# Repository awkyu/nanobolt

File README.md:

# nanobolt
This project is a proposal for the design of an ablation probe for osteoid osteoma using a new ablation technique proposed by Pavitra Krishnaswamy, Andras Kuthi, P. Thomas Vernier, and Martin A. Gundersen [[1]](https://doi.org/10.1109/TDEI.2007.4286518).

Surgical resection and thermal ablation techniques have been shown to have suboptimal efficacy for the treatment of osteoid osteomas due to the high risk of complications and large ablation zones. Ablation technologies that utilize electric fields instead of thermal energy to produce nanosized pores in tumor cell membranes have been shown to be an attractive method for treating a wide variety of cancers due to the short ablation times and non-invasive nature of the procedure. We propose a nanosecond pulse electric field ablation system utilizing a pulse generator as a compact solution to ablate osteoid osteomas without harming the healthy bone, leading to reduced instances of post-operative complications. 

[1] P. Krishnaswamy, A. Kuthi, P. T. Vernier and M. A. Gundersen, "Compact Subnanosecond Pulse Generator Using Avalanche Transistors for Cell Electroperturbation Studies," IEEE Transactions on Dielectrics and Electrical Insulation, vol. 14, no. 4, pp. 873-877, Aug. 2007, doi: 10.1109/TDEI.2007.4286518.

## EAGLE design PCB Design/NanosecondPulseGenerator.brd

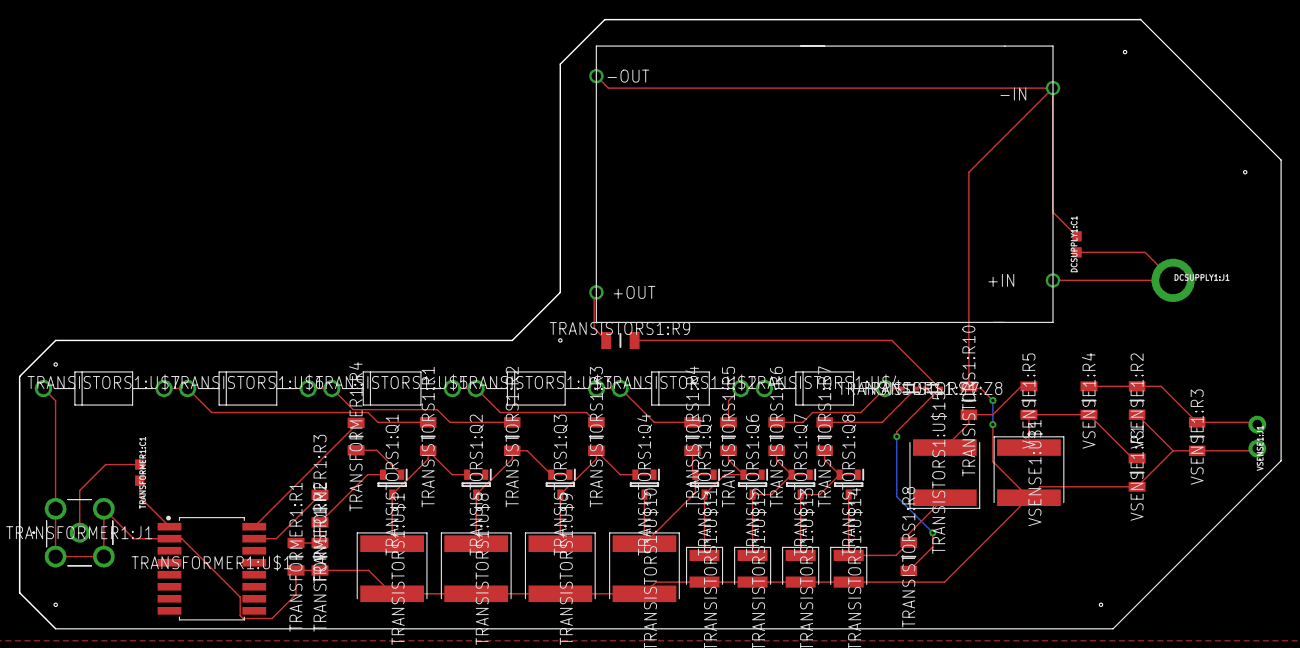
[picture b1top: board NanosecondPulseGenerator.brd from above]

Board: 2 copper layers, 133.3 x 64.4 mm, 52 parts (0 on the bottom side), 28 nets.

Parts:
DCSUPPLY1:C1: 0.1uF; 0603
DCSUPPLY1:J1: SNAP-FEMALE
DCSUPPLY1:U$1: DC-DCCONVERTER; DC-CONVERTER
TRANSFORMER1:C1: 10nF; 0603
TRANSFORMER1:J1: CONSMA008-G; CONSMA008G
TRANSFORMER1:R1, TRANSFORMER1:R2, TRANSFORMER1:R3, TRANSFORMER1:R4: CRCW12068R20FKEAHP; RESC3116X65N
TRANSFORMER1:U$1: TX1:1_QUAD; SOIC127P1067X508-16N
TRANSISTORS1:Q1, TRANSISTORS1:Q2, TRANSISTORS1:Q3, TRANSISTORS1:Q4, TRANSISTORS1:Q5, TRANSISTORS1:Q6, TRANSISTORS1:Q7, TRANSISTORS1:Q8: FMMT417TD; SOT96P240X110-3N
TRANSISTORS1:R1, TRANSISTORS1:R2, TRANSISTORS1:R3, TRANSISTORS1:R4, TRANSISTORS1:R5, TRANSISTORS1:R6, TRANSISTORS1:R7, TRANSISTORS1:R8: PTN1206Y1001BST1; RESC3216X84N
TRANSISTORS1:R9: CRCW1206182KFKEA; RESC3216X60N
TRANSISTORS1:R10: PATT1206E50R0BGT1; RESC3216X46N
TRANSISTORS1:U$1: CAP_120PF; CAPCP5963X368N
TRANSISTORS1:U$2, TRANSISTORS1:U$3, TRANSISTORS1:U$4, TRANSISTORS1:U$5, TRANSISTORS1:U$6, TRANSISTORS1:U$7: JANTX1N4993; DIOAD1274W101L533D349B
TRANSISTORS1:U$8: CAP_18PF; CAPCP5963X368N
TRANSISTORS1:U$9, TRANSISTORS1:U$15: CAP_6.8PF; CAPCP5963X368N
TRANSISTORS1:U$10: CAP_3.3PF; CAPCP5963X368N
TRANSISTORS1:U$11: CAP_2.2PF; CAPCP2927X200N
TRANSISTORS1:U$12: CAP_1.5PF; CAPCP2927X178N
TRANSISTORS1:U$13: CAP_1.0PF; CAPCP2927X178N
TRANSISTORS1:U$14: CAP_0.8PF; CAPCP2927X178N
TRANSISTORS1:Z7, TRANSISTORS1:Z8: MM5Z4685T1G; SODFL1608X70N
VSENSE1:J1: 1X02_NO_SILK
VSENSE1:R1: CRCW1206105RFKEA; RESC3216X60N
VSENSE1:R2, VSENSE1:R3: PATT1206E50R0BGT1; RESC3216X46N
VSENSE1:R4: CRCW1206255RFKEA; RESC3216X60N
VSENSE1:R5: CRCW12068K25FKEA; RESC3216X60N
VSENSE1:U$1: CAP_12PF; CAPCP5963X368N

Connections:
BASE: TRANSFORMER1:R4.1, TRANSISTORS1:Q1.1
DCSUPPLY1:N$1: DCSUPPLY1:C1.1, DCSUPPLY1:J1.1, DCSUPPLY1:U$1.+IN
EMIT: TRANSFORMER1:R1.2, TRANSFORMER1:R2.2, TRANSFORMER1:R3.1, TRANSISTORS1:Q1.2
GND: DCSUPPLY1:C1.2, DCSUPPLY1:U$1.-IN, DCSUPPLY1:U$1.-OUT, TRANSFORMER1:J1.2, TRANSFORMER1:J1.3, TRANSFORMER1:J1.4, TRANSFORMER1:J1.5, TRANSFORMER1:R1.1, TRANSFORMER1:R2.1, TRANSFORMER1:U$1.2, TRANSISTORS1:R10.1, TRANSISTORS1:U$1.2, TRANSISTORS1:U$7.C, TRANSISTORS1:U$8.2, TRANSISTORS1:U$9.2, TRANSISTORS1:U$10.2, TRANSISTORS1:U$11.2, TRANSISTORS1:U$12.2, TRANSISTORS1:U$13.2, TRANSISTORS1:U$14.2, VSENSE1:J1.2, VSENSE1:R1.1, VSENSE1:R2.1, VSENSE1:R3.1, VSENSE1:U$1.2
unnamed: DCSUPPLY1:U$1.+OUT, TRANSISTORS1:R9.2
OUT: TRANSISTORS1:R10.2, TRANSISTORS1:U$15.2, VSENSE1:R5.1
TRANSFORMER1:N$1: TRANSFORMER1:R4.2, TRANSFORMER1:U$1.16
TRANSFORMER1:N$2: TRANSFORMER1:C1.1, TRANSFORMER1:J1.1
TRANSFORMER1:N$3: TRANSFORMER1:C1.2, TRANSFORMER1:U$1.1
TRANSFORMER1:N$4: TRANSFORMER1:R3.2, TRANSFORMER1:U$1.15
TRANSISTORS1:N$1: TRANSISTORS1:Q1.3, TRANSISTORS1:Q2.1, TRANSISTORS1:Q2.2, TRANSISTORS1:R1.1, TRANSISTORS1:U$1.1
TRANSISTORS1:N$2: TRANSISTORS1:R8.2, TRANSISTORS1:R9.1, TRANSISTORS1:Z8.1
TRANSISTORS1:N$4: TRANSISTORS1:Q4.3, TRANSISTORS1:Q5.1, TRANSISTORS1:Q5.2, TRANSISTORS1:R4.1, TRANSISTORS1:U$10.1
TRANSISTORS1:N$8: TRANSISTORS1:R3.2, TRANSISTORS1:U$3.C, TRANSISTORS1:U$5.A
TRANSISTORS1:N$9: TRANSISTORS1:Q2.3, TRANSISTORS1:Q3.1, TRANSISTORS1:Q3.2, TRANSISTORS1:R2.1, TRANSISTORS1:U$8.1
TRANSISTORS1:N$10: TRANSISTORS1:Q3.3, TRANSISTORS1:Q4.1, TRANSISTORS1:Q4.2, TRANSISTORS1:R3.1, TRANSISTORS1:U$9.1
TRANSISTORS1:N$12: TRANSISTORS1:Q5.3, TRANSISTORS1:Q6.1, TRANSISTORS1:Q6.2, TRANSISTORS1:R5.1, TRANSISTORS1:U$11.1
TRANSISTORS1:N$13: TRANSISTORS1:Q6.3, TRANSISTORS1:Q7.1, TRANSISTORS1:Q7.2, TRANSISTORS1:R6.1, TRANSISTORS1:U$12.1
TRANSISTORS1:N$14: TRANSISTORS1:Q7.3, TRANSISTORS1:Q8.1, TRANSISTORS1:Q8.2, TRANSISTORS1:R7.1, TRANSISTORS1:U$13.1
TRANSISTORS1:N$15: TRANSISTORS1:Q8.3, TRANSISTORS1:R8.1, TRANSISTORS1:U$14.1, TRANSISTORS1:U$15.1
TRANSISTORS1:N$16: TRANSISTORS1:R7.2, TRANSISTORS1:Z7.1, TRANSISTORS1:Z8.2
TRANSISTORS1:N$17: TRANSISTORS1:R6.2, TRANSISTORS1:U$4.A, TRANSISTORS1:Z7.2
TRANSISTORS1:N$18: TRANSISTORS1:R4.2, TRANSISTORS1:U$2.C, TRANSISTORS1:U$3.A
TRANSISTORS1:N$19: TRANSISTORS1:R2.2, TRANSISTORS1:U$5.C, TRANSISTORS1:U$6.A
TRANSISTORS1:N$20: TRANSISTORS1:R1.2, TRANSISTORS1:U$6.C, TRANSISTORS1:U$7.A
TRANSISTORS1:N$22: TRANSISTORS1:R5.2, TRANSISTORS1:U$2.A, TRANSISTORS1:U$4.C
VSENSE1:N$1: VSENSE1:J1.1, VSENSE1:R2.2, VSENSE1:R3.2, VSENSE1:R4.2
VSENSE1:N$2: VSENSE1:R1.2, VSENSE1:R4.1, VSENSE1:R5.2, VSENSE1:U$1.1

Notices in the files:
parts and their libraries:
SparkFun-Capacitors: Licensing: Creative Commons ShareAlike 4.0 International - https://creativecommons.org/licenses/by-sa/4.0
